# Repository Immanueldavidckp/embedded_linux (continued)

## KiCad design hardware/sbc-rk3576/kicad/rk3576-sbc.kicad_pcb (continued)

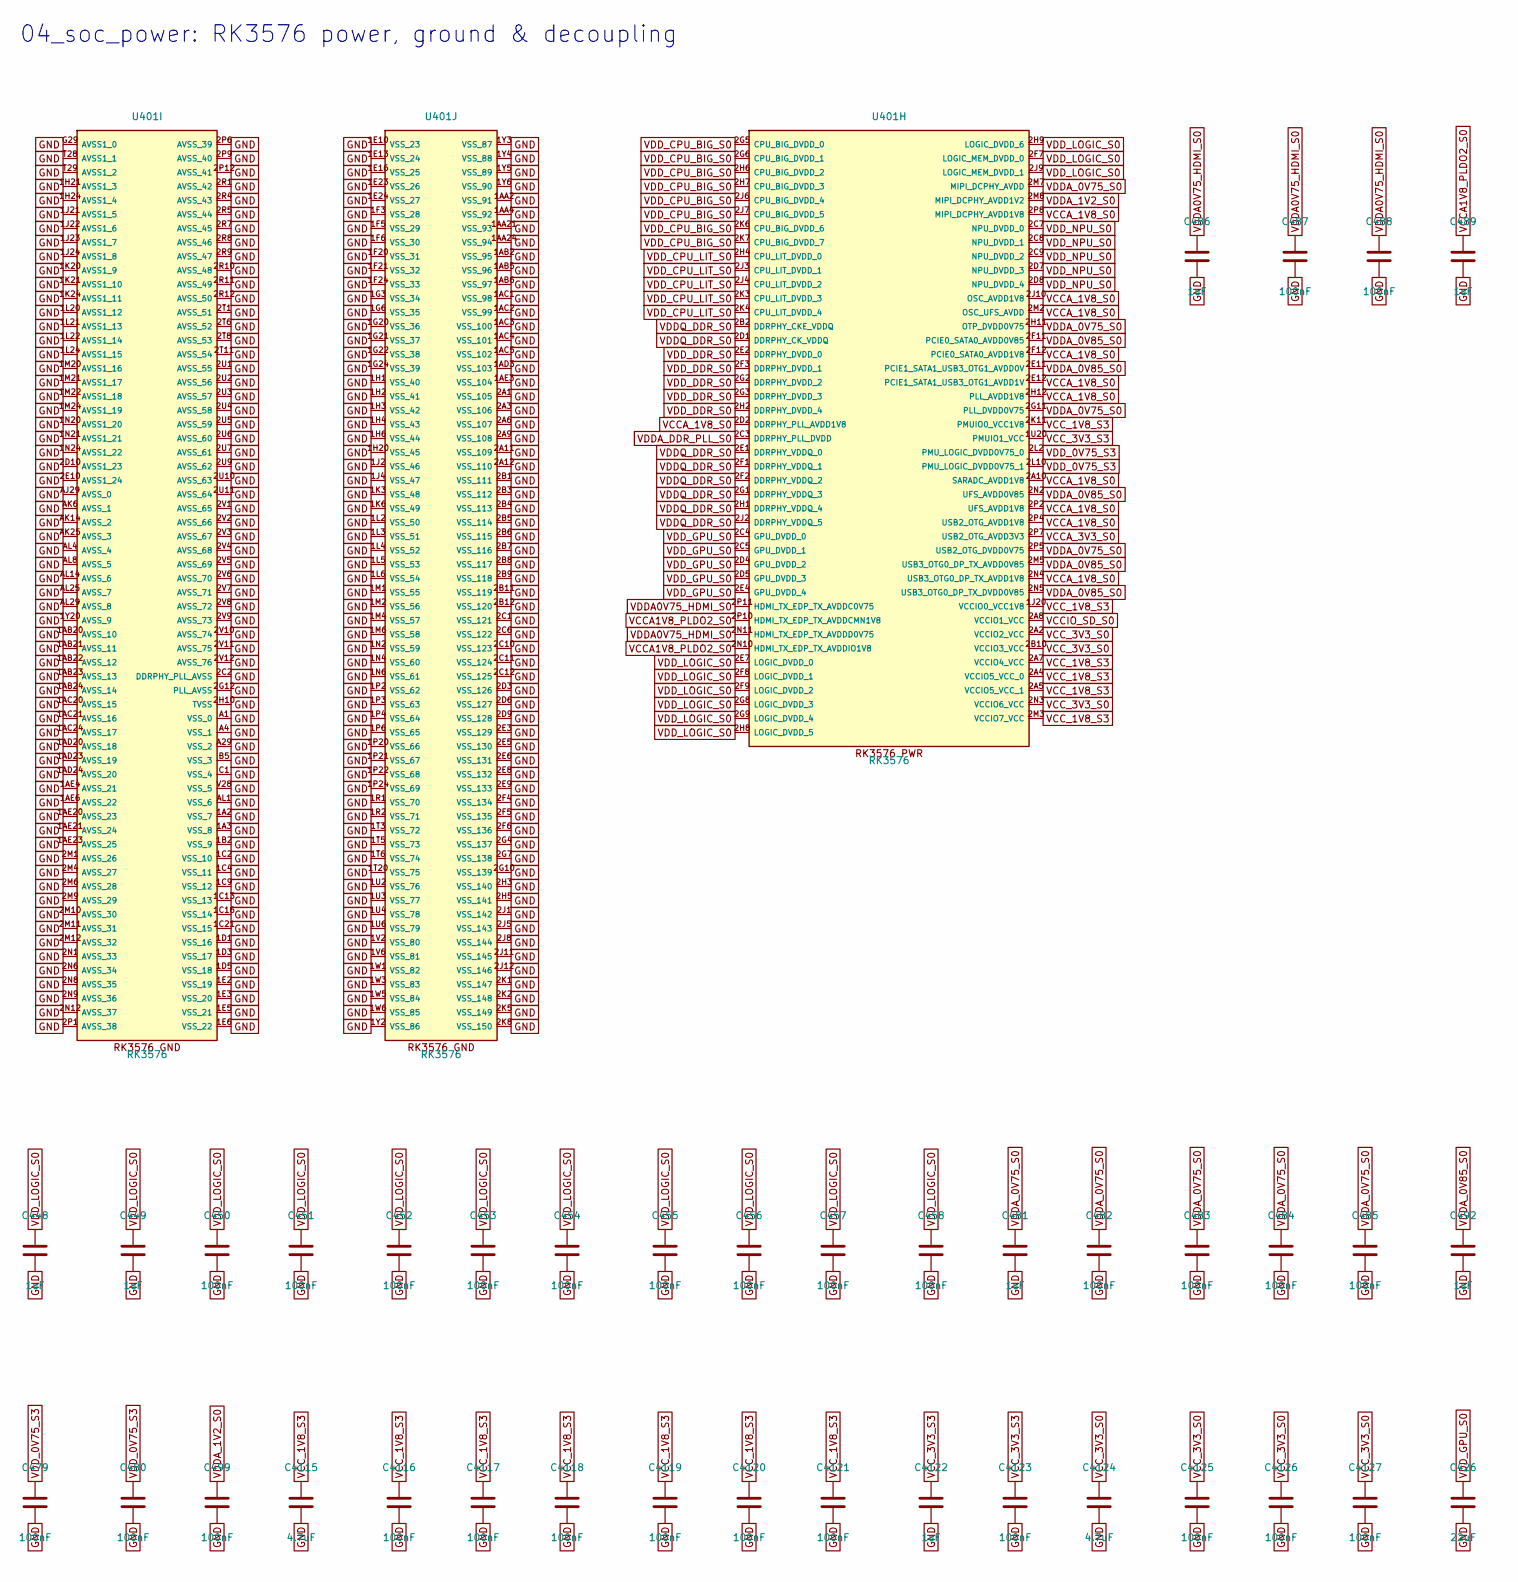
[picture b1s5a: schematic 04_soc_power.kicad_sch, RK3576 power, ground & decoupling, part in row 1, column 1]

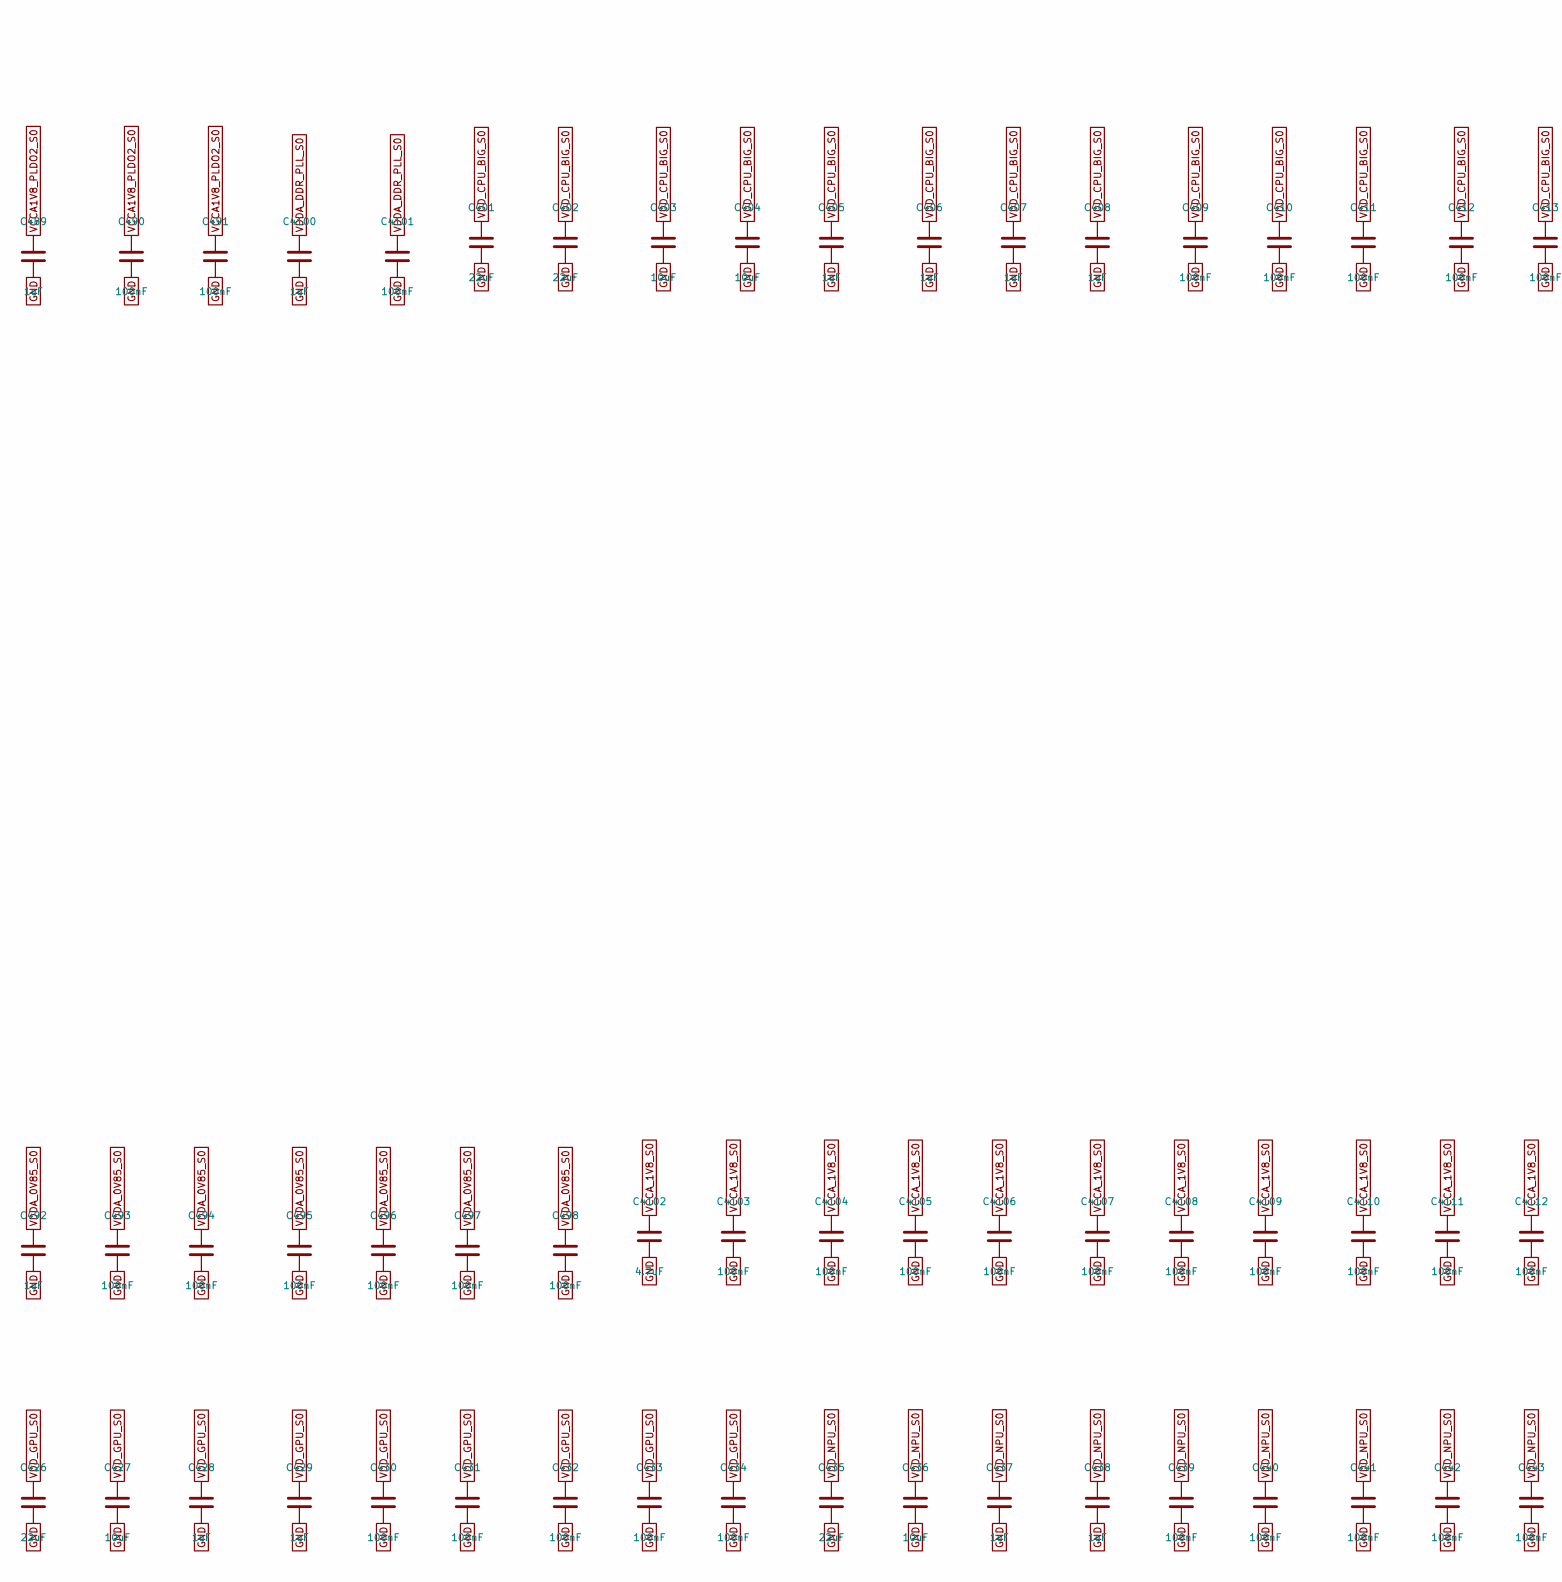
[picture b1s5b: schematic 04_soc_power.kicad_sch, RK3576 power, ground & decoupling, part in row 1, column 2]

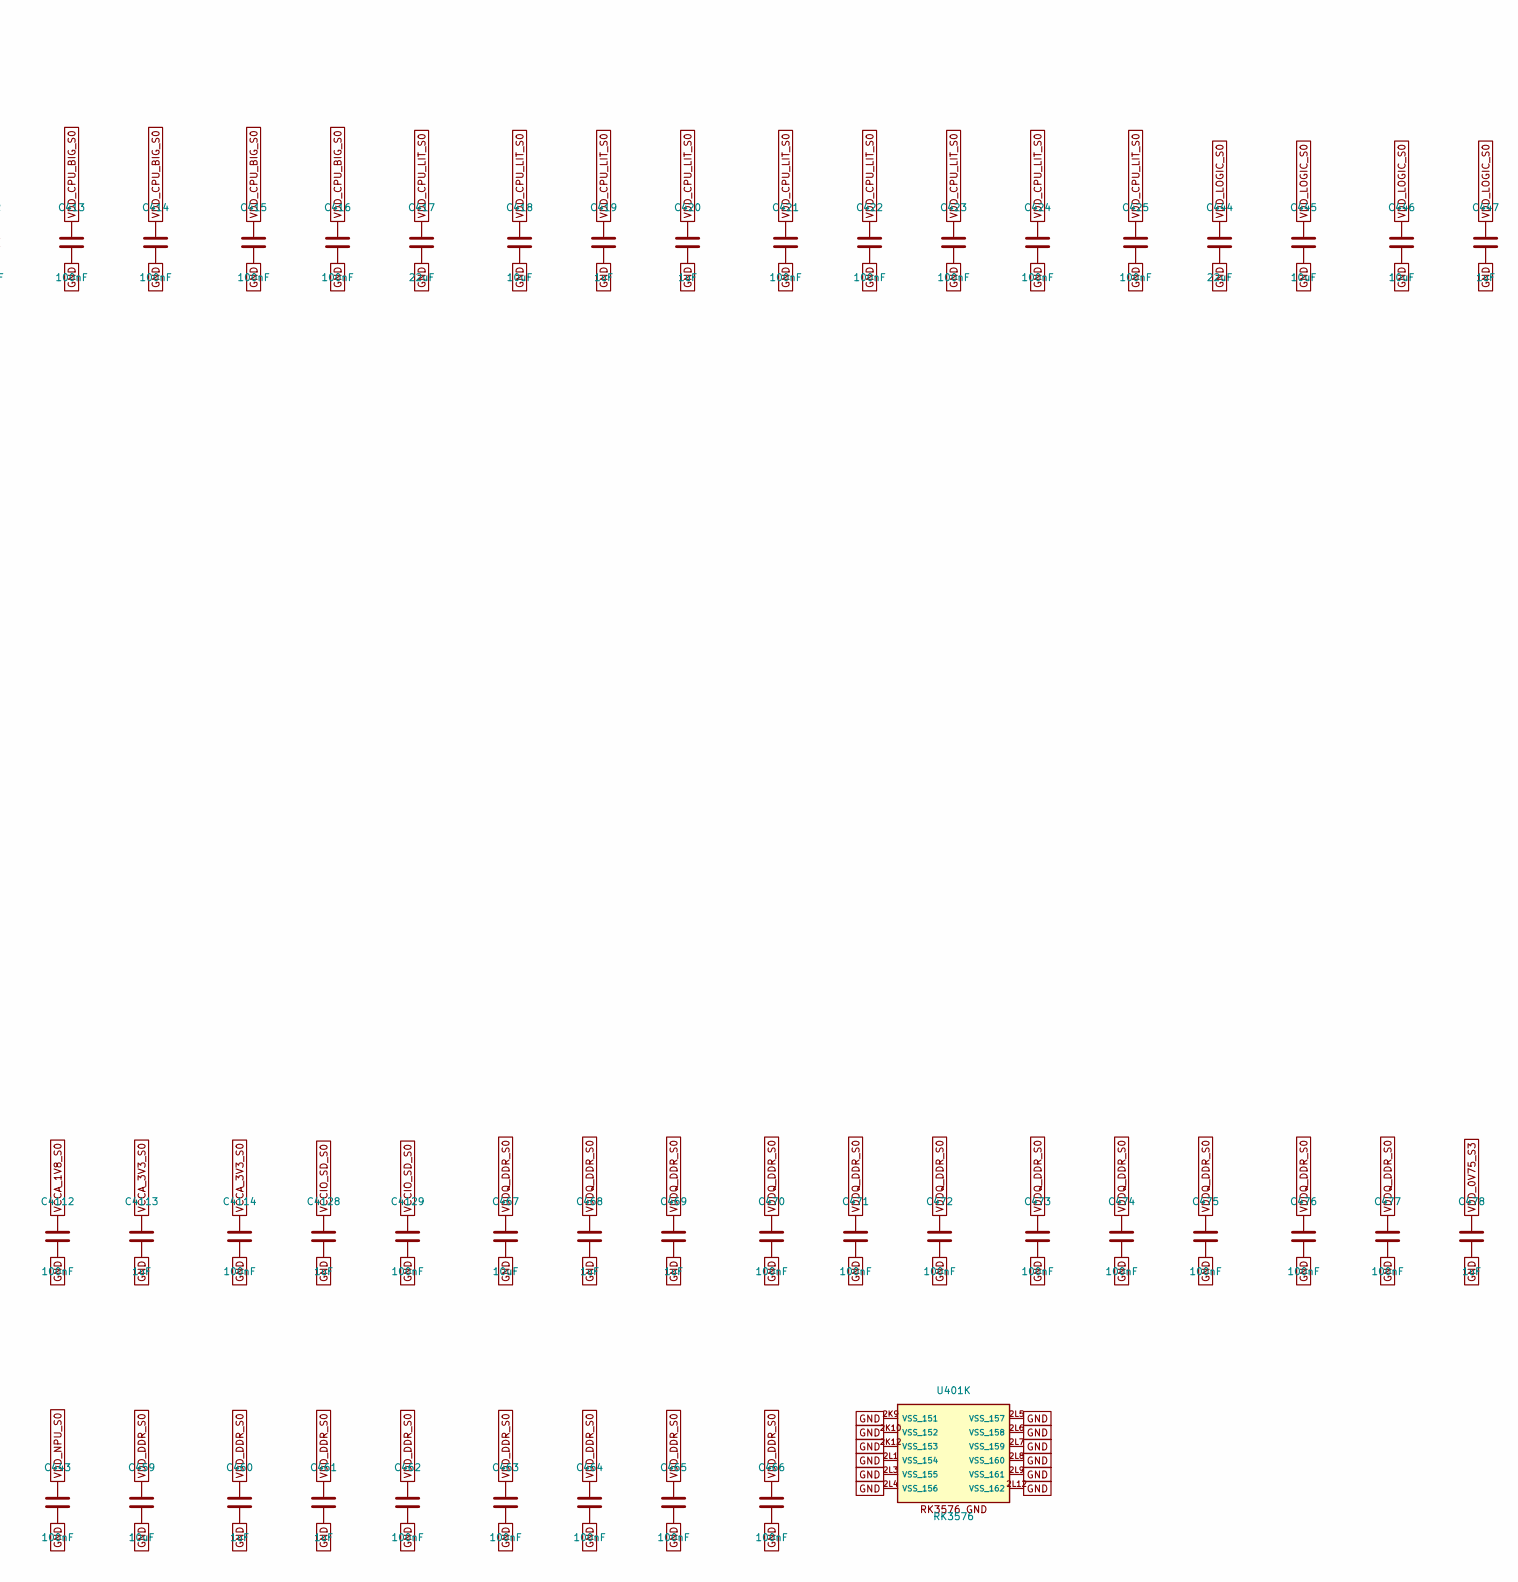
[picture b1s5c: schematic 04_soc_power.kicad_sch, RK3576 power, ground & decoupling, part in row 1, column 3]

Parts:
C401, C402, C417, C426, C435, C444: 22uF; C_0603_1608Metric; MPN 0603 22uF 10V X5R
C403, C404, C418, C427, C436, C445, C446, C459, C467: 10uF; C_0603_1608Metric; MPN 0603 10uF 10V X5R
C405, C406, C407, C408, C419, C420, C428, C429, C437, C438, C447, C448, C449, C460, C461, C468, C469, C478, C481, C486, C489, C492, C4100, C4113, C4122, C4128: 1uF; C_0402_1005Metric; MPN 0402 1uF 6.3V X5R
C409, C410, C411, C412, C413, C414, C415, C416, C421, C422, C423, C424, C425, C430, C431, C432, C433, C434, C439, C440, C441, C442, C443, C450, C451, C452, C453, C454, C455, C456, C457, C458, C462, C463, C464, C465, C466, C470, C471, C472, C473, C474, C475, C476, C477, C479, C480, C482, C483, C484, C485, C487, C488, C490, C491, C493, C494, C495, C496, C497, C498, C499, C4101, C4103, C4104, C4105, C4106, C4107, C4108, C4109, C4110, C4111, C4112, C4114, C4116, C4117, C4118, C4119, C4120, C4121, C4123, C4125, C4126, C4127, C4129: 100nF; C_0402_1005Metric; MPN 0402 100nF 6.3V X5R
C4102, C4115, C4124: 4.7uF; C_0402_1005Metric; MPN 0402 4.7uF 10V X5R
U401: RK3576; RK3576_FCCSP-698_16.1x17.2mm; MPN RK3576

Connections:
GND: C401.2, C402.2, C403.2, C404.2, C405.2, C406.2, C407.2, C408.2, C409.2, C410.2, C411.2, C412.2, C413.2, C414.2, C415.2, C416.2, C417.2, C418.2, C419.2, C420.2, C421.2, C422.2, C423.2, C424.2, C425.2, C426.2, C427.2, C428.2, C429.2, C430.2, C431.2, C432.2, C433.2, C434.2, C435.2, C436.2, C437.2, C438.2, C439.2, C440.2, C441.2, C442.2, C443.2, C444.2, C445.2, C446.2, C447.2, C448.2, C449.2, C450.2, C451.2, C452.2, C453.2, C454.2, C455.2, C456.2, C457.2, C458.2, C459.2, C460.2, C461.2, C462.2, C463.2, C464.2, C465.2, C466.2, C467.2, C468.2, C469.2, C470.2, C471.2, C472.2, C473.2, C474.2, C475.2, C476.2, C477.2, C478.2, C479.2, C480.2, C481.2, C482.2, C483.2, C484.2, C485.2, C486.2, C487.2, C488.2, C489.2, C490.2, C491.2, C492.2, C493.2, C494.2, C495.2, C496.2, C497.2, C498.2, C499.2, C4100.2, C4101.2, C4102.2, C4103.2, C4104.2, C4105.2, C4106.2, C4107.2, C4108.2, C4109.2, C4110.2, C4111.2, C4112.2, C4113.2, C4114.2, C4115.2, C4116.2, C4117.2, C4118.2, C4119.2, C4120.2, C4121.2, C4122.2, C4123.2, C4124.2, C4125.2, C4126.2, C4127.2, C4128.2, C4129.2, U401.1A2 (VSS_7), U401.1A3 (VSS_8), U401.1AA2 (VSS_91), U401.1AA4 (VSS_92), U401.1AA21 (VSS_93), U401.1AA24 (VSS_94), U401.1AB2 (VSS_95), U401.1AB5 (VSS_96), U401.1AB6 (VSS_97), U401.1AB20 (AVSS_10), U401.1AB21 (AVSS_11), U401.1AB22 (AVSS_12), U401.1AB23 (AVSS_13), U401.1AB24 (AVSS_14), U401.1AC1 (VSS_98), U401.1AC2 (VSS_99), U401.1AC3 (VSS_100), U401.1AC4 (VSS_101), U401.1AC5 (VSS_102), U401.1AC20 (AVSS_15), U401.1AC21 (AVSS_16), U401.1AC24 (AVSS_17), U401.1AD3 (VSS_103), U401.1AD20 (AVSS_18), U401.1AD23 (AVSS_19), U401.1AD24 (AVSS_20), U401.1AE3 (VSS_104), U401.1AE4 (AVSS_21), U401.1AE6 (AVSS_22), U401.1AE20 (AVSS_23), U401.1AE21 (AVSS_24), U401.1AE23 (AVSS_25), U401.1B2 (VSS_9), U401.1C2 (VSS_10), U401.1C4 (VSS_11), U401.1C9 (VSS_12), U401.1C13 (VSS_13), U401.1C16 (VSS_14), U401.1C21 (VSS_15), U401.1D1 (VSS_16), U401.1D3 (VSS_17), U401.1D5 (VSS_18), U401.1E2 (VSS_19), U401.1E3 (VSS_20), U401.1E5 (VSS_21), U401.1E6 (VSS_22), U401.1E10 (VSS_23), U401.1E13 (VSS_24), U401.1E16 (VSS_25), U401.1E23 (VSS_26), U401.1E24 (VSS_27), U401.1F3 (VSS_28), U401.1F5 (VSS_29), U401.1F6 (VSS_30), U401.1F20 (VSS_31), U401.1F21 (VSS_32), U401.1F24 (VSS_33), U401.1G3 (VSS_34), U401.1G6 (VSS_35), U401.1G20 (VSS_36), U401.1G21 (VSS_37), U401.1G22 (VSS_38), U401.1G24 (VSS_39), U401.1H1 (VSS_40), U401.1H2 (VSS_41), U401.1H3 (VSS_42), U401.1H4 (VSS_43), U401.1H6 (VSS_44), U401.1H20 (VSS_45), U401.1H21 (AVSS1_3), U401.1H24 (AVSS1_4), U401.1J2 (VSS_46), U401.1J4 (VSS_47), U401.1J21 (AVSS1_5), U401.1J22 (AVSS1_6), U401.1J23 (AVSS1_7), U401.1J24 (AVSS1_8), U401.1K3 (VSS_48), U401.1K6 (VSS_49), U401.1K20 (AVSS1_9), U401.1K21 (AVSS1_10), U401.1K24 (AVSS1_11), U401.1L2 (VSS_50), U401.1L3 (VSS_51), U401.1L4 (VSS_52), U401.1L5 (VSS_53), U401.1L6 (VSS_54), U401.1L20 (AVSS1_12), U401.1L21 (AVSS1_13), U401.1L22 (AVSS1_14), U401.1L24 (AVSS1_15), U401.1M1 (VSS_55), U401.1M2 (VSS_56), U401.1M4 (VSS_57), U401.1M6 (VSS_58), U401.1M20 (AVSS1_16), U401.1M21 (AVSS1_17), U401.1M22 (AVSS1_18), U401.1M24 (AVSS1_19), U401.1N2 (VSS_59), U401.1N4 (VSS_60), U401.1N6 (VSS_61), U401.1N20 (AVSS1_20), U401.1N21 (AVSS1_21), U401.1N24 (AVSS1_22), U401.1P2 (VSS_62), U401.1P3 (VSS_63), U401.1P4 (VSS_64), U401.1P6 (VSS_65), U401.1P20 (VSS_66), U401.1P21 (VSS_67), U401.1P22 (VSS_68), U401.1P24 (VSS_69), U401.1R1 (VSS_70), U401.1R2 (VSS_71), U401.1T3 (VSS_72), U401.1T5 (VSS_73), U401.1T6 (VSS_74), U401.1T20 (VSS_75), U401.1U2 (VSS_76), U401.1U3 (VSS_77), U401.1U4 (VSS_78), U401.1U6 (VSS_79), U401.1V2 (VSS_80), U401.1V6 (VSS_81), U401.1W1 (VSS_82), U401.1W3 (VSS_83), U401.1W5 (VSS_84), U401.1W6 (VSS_85), U401.1Y2 (VSS_86), U401.1Y3 (VSS_87), U401.1Y4 (VSS_88), U401.1Y5 (VSS_89), U401.1Y6 (VSS_90), U401.1Y20 (AVSS_9), U401.2A1 (VSS_105), U401.2A3 (VSS_106), U401.2A6 (VSS_107), U401.2A9 (VSS_108), U401.2A11 (VSS_109), U401.2A12 (VSS_110), U401.2B1 (VSS_111), U401.2B3 (VSS_112), U401.2B4 (VSS_113), U401.2B5 (VSS_114), U401.2B6 (VSS_115), U401.2B7 (VSS_116), U401.2B8 (VSS_117), U401.2B9 (VSS_118), U401.2B11 (VSS_119), U401.2B12 (VSS_120), U401.2C1 (VSS_121), U401.2C2 (DDRPHY_PLL_AVSS), U401.2C6 (VSS_122), U401.2C10 (VSS_123), U401.2C11 (VSS_124), U401.2C12 (VSS_125), U401.2D3 (VSS_126), U401.2D6 (VSS_127), U401.2D9 (VSS_128), U401.2D10 (AVSS1_23), U401.2E3 (VSS_129), U401.2E5 (VSS_130), U401.2E6 (VSS_131), U401.2E8 (VSS_132), U401.2E9 (VSS_133), U401.2E10 (AVSS1_24), U401.2F4 (VSS_134), U401.2F5 (VSS_135), U401.2F6 (VSS_136), U401.2G4 (VSS_137), U401.2G7 (VSS_138), U401.2G10 (VSS_139), U401.2G12 (PLL_AVSS), U401.2H3 (VSS_140), U401.2H5 (VSS_141), U401.2H10 (TVSS), U401.2J1 (VSS_142), U401.2J5 (VSS_143), U401.2J8 (VSS_144), U401.2J11 (VSS_145), U401.2J12 (VSS_146), U401.2K1 (VSS_147), U401.2K2 (VSS_148), U401.2K5 (VSS_149), U401.2K8 (VSS_150), U401.2K9 (VSS_151), U401.2K10 (VSS_152), U401.2K12 (VSS_153), U401.2L1 (VSS_154), U401.2L3 (VSS_155), U401.2L4 (VSS_156), U401.2L5 (VSS_157), U401.2L6 (VSS_158), U401.2L7 (VSS_159), U401.2L8 (VSS_160), U401.2L9 (VSS_161), U401.2L12 (VSS_162), U401.2M1 (AVSS_26), U401.2M4 (AVSS_27), U401.2M6 (AVSS_28), U401.2M9 (AVSS_29), U401.2M10 (AVSS_30), U401.2M11 (AVSS_31), U401.2M12 (AVSS_32), U401.2N1 (AVSS_33), U401.2N6 (AVSS_34), U401.2N8 (AVSS_35), U401.2N9 (AVSS_36), U401.2N12 (AVSS_37), U401.2P1 (AVSS_38), U401.2P6 (AVSS_39), U401.2P9 (AVSS_40), U401.2P12 (AVSS_41), U401.2R1 (AVSS_42), U401.2R4 (AVSS_43), U401.2R5 (AVSS_44), U401.2R7 (AVSS_45), U401.2R8 (AVSS_46), U401.2R9 (AVSS_47), U401.2R10 (AVSS_48), U401.2R11 (AVSS_49), U401.2R12 (AVSS_50), U401.2T1 (AVSS_51), U401.2T6 (AVSS_52), U401.2T8 (AVSS_53), U401.2T11 (AVSS_54), U401.2U1 (AVSS_55), U401.2U2 (AVSS_56), U401.2U3 (AVSS_57), U401.2U4 (AVSS_58), U401.2U5 (AVSS_59), U401.2U6 (AVSS_60), U401.2U7 (AVSS_61), U401.2U9 (AVSS_62), U401.2U10 (AVSS_63), U401.2U11 (AVSS_64), U401.2V1 (AVSS_65), U401.2V2 (AVSS_66), U401.2V3 (AVSS_67), U401.2V4 (AVSS_68), U401.2V5 (AVSS_69), U401.2V6 (AVSS_70), U401.2V7 (AVSS_71), U401.2V8 (AVSS_72), U401.2V9 (AVSS_73), U401.2V10 (AVSS_74), U401.2V11 (AVSS_75), U401.2V12 (AVSS_76), U401.A1 (VSS_0), U401.A4 (VSS_1), U401.A29 (VSS_2), U401.AJ29 (AVSS_0), U401.AK6 (AVSS_1), U401.AK14 (AVSS_2), U401.AK25 (AVSS_3), U401.AL1 (VSS_6), U401.AL4 (AVSS_4), U401.AL8 (AVSS_5), U401.AL14 (AVSS_6), U401.AL25 (AVSS_7), U401.AL29 (AVSS_8), U401.B5 (VSS_3), U401.C1 (VSS_4), U401.G29 (AVSS1_0), U401.T28 (AVSS1_1), U401.T29 (AVSS1_2), U401.V28 (VSS_5); also elsewhere on the board
VCCA1V8_PLDO2_S0: C489.1, C490.1, C491.1, U401.2N10 (HDMI_TX_EDP_TX_AVDDIO1V8), U401.2P10 (HDMI_TX_EDP_TX_AVDDCMN1V8); also elsewhere on the board
VCCA_1V8_S0: C4102.1, C4103.1, C4104.1, C4105.1, C4106.1, C4107.1, C4108.1, C4109.1, C4110.1, C4111.1, C4112.1, U401.2A10 (SARADC_AVDD1V8), U401.2D2 (DDRPHY_PLL_AVDD1V8), U401.2E12 (PCIE1_SATA1_USB3_OTG1_AVDD1V), U401.2F12 (PCIE0_SATA0_AVDD1V8), U401.2H12 (PLL_AVDD1V8), U401.2J10 (OSC_AVDD1V8), U401.2M2 (OSC_UFS_AVDD), U401.2N4 (USB3_OTG0_DP_TX_AVDD1V8), U401.2P2 (UFS_AVDD1V8), U401.2P4 (USB2_OTG_AVDD1V8), U401.2P8 (MIPI_DCPHY_AVDD1V8); also elsewhere on the board
VCCA_3V3_S0: C4113.1, C4114.1, U401.2P7 (USB2_OTG_AVDD3V3); also elsewhere on the board
VCCIO_SD_S0: C4128.1, C4129.1, U401.2A8 (VCCIO1_VCC); also elsewhere on the board
VCC_1V8_S3: C4115.1, C4116.1, C4117.1, C4118.1, C4119.1, C4120.1, C4121.1, U401.1J20 (VCCIO0_VCC1V8), U401.2A4 (VCCIO5_VCC_0), U401.2A5 (VCCIO5_VCC_1), U401.2A7 (VCCIO4_VCC), U401.2K11 (PMUIO0_VCC1V8), U401.2M3 (VCCIO7_VCC); also elsewhere on the board
VCC_3V3_S0: C4124.1, C4125.1, C4126.1, C4127.1, U401.2A2 (VCCIO2_VCC), U401.2B10 (VCCIO3_VCC), U401.2N3 (VCCIO6_VCC); also elsewhere on the board
VCC_3V3_S3: C4122.1, C4123.1, U401.1U20 (PMUIO1_VCC); also elsewhere on the board
VDDA0V75_HDMI_S0: C486.1, C487.1, C488.1, U401.2N11 (HDMI_TX_EDP_TX_AVDDD0V75), U401.2P11 (HDMI_TX_EDP_TX_AVDDC0V75); also elsewhere on the board
VDDA_0V75_S0: C481.1, C482.1, C483.1, C484.1, C485.1, U401.2G11 (PLL_DVDD0V75), U401.2H11 (OTP_DVDD0V75), U401.2M7 (MIPI_DCPHY_AVDD), U401.2P5 (USB2_OTG_DVDD0V75); also elsewhere on the board
VDDA_0V85_S0: C492.1, C493.1, C494.1, C495.1, C496.1, C497.1, C498.1, U401.2E11 (PCIE1_SATA1_USB3_OTG1_AVDD0V), U401.2F11 (PCIE0_SATA0_AVDD0V85), U401.2M5 (USB3_OTG0_DP_TX_AVDD0V85), U401.2N2 (UFS_AVDD0V85), U401.2N5 (USB3_OTG0_DP_TX_DVDD0V85); also elsewhere on the board
VDDA_1V2_S0: C499.1, U401.2M8 (MIPI_DCPHY_AVDD1V2); also elsewhere on the board
VDDA_DDR_PLL_S0: C4100.1, C4101.1, U401.2C3 (DDRPHY_PLL_DVDD); also elsewhere on the board
VDDQ_DDR_S0: C467.1, C468.1, C469.1, C470.1, C471.1, C472.1, C473.1, C474.1, C475.1, C476.1, C477.1, U401.2B2 (DDRPHY_CKE_VDDQ), U401.2D1 (DDRPHY_CK_VDDQ), U401.2E1 (DDRPHY_VDDQ_0), U401.2F1 (DDRPHY_VDDQ_1), U401.2F2 (DDRPHY_VDDQ_2), U401.2G1 (DDRPHY_VDDQ_3), U401.2H1 (DDRPHY_VDDQ_4), U401.2J2 (DDRPHY_VDDQ_5); also elsewhere on the board
VDD_0V75_S3: C478.1, C479.1, C480.1, U401.2L2 (PMU_LOGIC_DVDD0V75_0), U401.2L10 (PMU_LOGIC_DVDD0V75_1); also elsewhere on the board
VDD_CPU_BIG_S0: C401.1, C402.1, C403.1, C404.1, C405.1, C406.1, C407.1, C408.1, C409.1, C410.1, C411.1, C412.1, C413.1, C414.1, C415.1, C416.1, U401.2G5 (CPU_BIG_DVDD_0), U401.2G6 (CPU_BIG_DVDD_1), U401.2H6 (CPU_BIG_DVDD_2), U401.2H7 (CPU_BIG_DVDD_3), U401.2J6 (CPU_BIG_DVDD_4), U401.2J7 (CPU_BIG_DVDD_5), U401.2K6 (CPU_BIG_DVDD_6), U401.2K7 (CPU_BIG_DVDD_7); also elsewhere on the board
VDD_CPU_LIT_S0: C417.1, C418.1, C419.1, C420.1, C421.1, C422.1, C423.1, C424.1, C425.1, U401.2H4 (CPU_LIT_DVDD_0), U401.2J3 (CPU_LIT_DVDD_1), U401.2J4 (CPU_LIT_DVDD_2), U401.2K3 (CPU_LIT_DVDD_3), U401.2K4 (CPU_LIT_DVDD_4); also elsewhere on the board
VDD_DDR_S0: C459.1, C460.1, C461.1, C462.1, C463.1, C464.1, C465.1, C466.1, U401.2E2 (DDRPHY_DVDD_0), U401.2F3 (DDRPHY_DVDD_1), U401.2G2 (DDRPHY_DVDD_2), U401.2G3 (DDRPHY_DVDD_3), U401.2H2 (DDRPHY_DVDD_4); also elsewhere on the board
VDD_GPU_S0: C426.1, C427.1, C428.1, C429.1, C430.1, C431.1, C432.1, C433.1, C434.1, U401.2C4 (GPU_DVDD_0), U401.2C5 (GPU_DVDD_1), U401.2D4 (GPU_DVDD_2), U401.2D5 (GPU_DVDD_3), U401.2E4 (GPU_DVDD_4); also elsewhere on the board
VDD_LOGIC_S0: C444.1, C445.1, C446.1, C447.1, C448.1, C449.1, C450.1, C451.1, C452.1, C453.1, C454.1, C455.1, C456.1, C457.1, C458.1, U401.2E7 (LOGIC_DVDD_0), U401.2F7 (LOGIC_MEM_DVDD_0), U401.2F8 (LOGIC_DVDD_1), U401.2F9 (LOGIC_DVDD_2), U401.2G8 (LOGIC_DVDD_3), U401.2G9 (LOGIC_DVDD_4), U401.2H8 (LOGIC_DVDD_5), U401.2H9 (LOGIC_DVDD_6), U401.2J9 (LOGIC_MEM_DVDD_1); also elsewhere on the board
VDD_NPU_S0: C435.1, C436.1, C437.1, C438.1, C439.1, C440.1, C441.1, C442.1, C443.1, U401.2C7 (NPU_DVDD_0), U401.2C8 (NPU_DVDD_1), U401.2C9 (NPU_DVDD_2), U401.2D7 (NPU_DVDD_3), U401.2D8 (NPU_DVDD_4); also elsewhere on the board

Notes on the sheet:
04_soc_power: RK3576 power, ground & decoupling

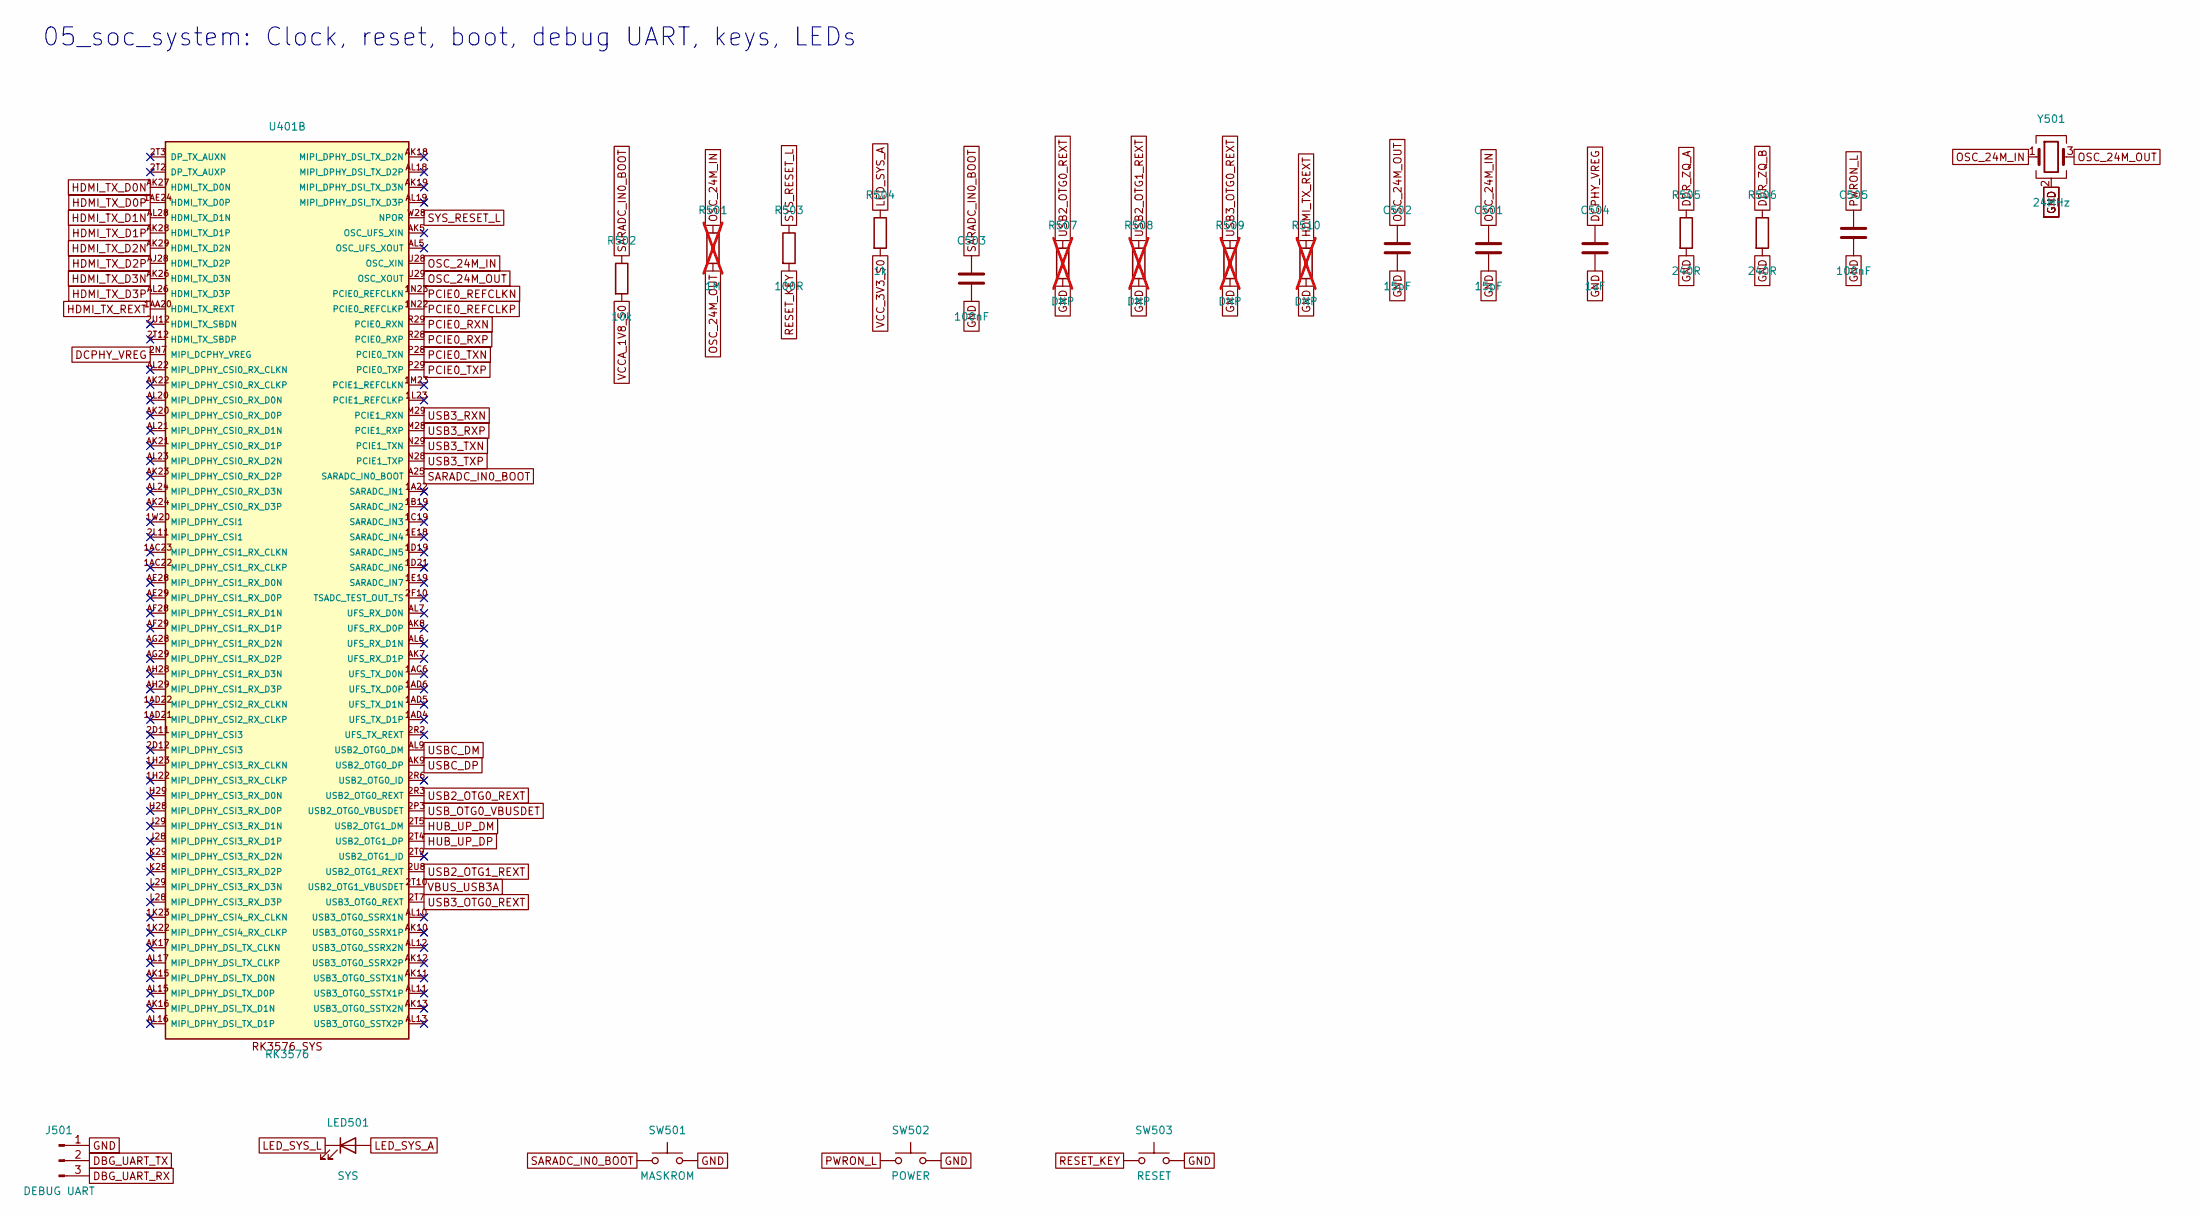
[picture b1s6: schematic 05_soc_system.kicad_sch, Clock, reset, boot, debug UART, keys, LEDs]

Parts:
C501, C502: 15pF; C_0402_1005Metric; MPN 0402 15pF 50V C0G
C503, C505: 100nF; C_0402_1005Metric; MPN 0402 100nF 6.3V X5R
C504: 1uF; C_0402_1005Metric; MPN 0402 1uF 6.3V X5R
J501: DEBUG UART; PinHeader_1x03_P2.54mm_Vertical; MPN 2.54mm 1x3 pin header
LED501: SYS; LED_0603_1608Metric; MPN 19-217/BHC-ZL1M2RY/3T; LCSC C72041
R501: 1M; R_0402_1005Metric; MPN 0402 1M 1%; not fitted
R502: 10k; R_0402_1005Metric; MPN 0402 10k 1%
R503: 100R; R_0402_1005Metric; MPN 0402 100R 1%
R504: 1k; R_0402_1005Metric; MPN 0402 1k 1%
R505, R506: 240R; R_0402_1005Metric; MPN 0402 240R 1%
R507, R508, R509, R510: DNP; R_0402_1005Metric; MPN 0402 DNP 1%; not fitted
SW501: MASKROM; SW_SPST_PTS810; MPN PTS810 SJM 250 SMTR LFS (alt XKB TS-108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
SW502: POWER; SW_SPST_PTS810; MPN PTS810 SJM 250 SMTR LFS (alt XKB TS-108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
SW503: RESET; SW_SPST_PTS810; MPN PTS810 SJM 250 SMTR LFS (alt XKB TS-108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
U401: RK3576; RK3576_FCCSP-698_16.1x17.2mm; MPN RK3576
Y501: 24MHz; Crystal_SMD_3225-4Pin_3.2x2.5mm; MPN X322524MOB4SI (24MHz 20pF 10ppm); LCSC C9002

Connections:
DBG_UART_RX: J501.3; also elsewhere on the board
DBG_UART_TX: J501.2; also elsewhere on the board
DCPHY_VREG: C504.1, U401.2N7 (MIPI_DCPHY_VREG)
DDR_ZQ_A: R505.1; also elsewhere on the board
DDR_ZQ_B: R506.1; also elsewhere on the board
GND: C501.2, C502.2, C503.2, C504.2, C505.2, J501.1, R505.2, R506.2, R507.2, R508.2, R509.2, R510.2, SW501.2, SW502.2, SW503.2, Y501.2 (G), Y501.4 (G); also elsewhere on the board
HDMI_TX_D0N: U401.AK27 (HDMI_TX_D0N); also elsewhere on the board
HDMI_TX_D0P: U401.1AE24 (HDMI_TX_D0P); also elsewhere on the board
HDMI_TX_D1N: U401.AL28 (HDMI_TX_D1N); also elsewhere on the board
HDMI_TX_D1P: U401.AK28 (HDMI_TX_D1P); also elsewhere on the board
HDMI_TX_D2N: U401.AK29 (HDMI_TX_D2N); also elsewhere on the board
HDMI_TX_D2P: U401.AJ28 (HDMI_TX_D2P); also elsewhere on the board
HDMI_TX_D3N: U401.AK26 (HDMI_TX_D3N); also elsewhere on the board
HDMI_TX_D3P: U401.AL26 (HDMI_TX_D3P); also elsewhere on the board
HDMI_TX_REXT: R510.1, U401.1AA20 (HDMI_TX_REXT)
HUB_UP_DM: U401.2T5 (USB2_OTG1_DM); also elsewhere on the board
HUB_UP_DP: U401.2T4 (USB2_OTG1_DP); also elsewhere on the board
LED_SYS_A: LED501.2 (A), R504.1
LED_SYS_L: LED501.1 (K); also elsewhere on the board
OSC_24M_IN: C501.1, R501.1, U401.U28 (OSC_XIN), Y501.1
OSC_24M_OUT: C502.1, R501.2, U401.U29 (OSC_XOUT), Y501.3
PCIE0_REFCLKN: U401.1N23 (PCIE0_REFCLKN); also elsewhere on the board
PCIE0_REFCLKP: U401.1N22 (PCIE0_REFCLKP); also elsewhere on the board
PCIE0_RXN: U401.R29 (PCIE0_RXN); also elsewhere on the board
PCIE0_RXP: U401.R28 (PCIE0_RXP); also elsewhere on the board
PCIE0_TXN: U401.P28 (PCIE0_TXN); also elsewhere on the board
PCIE0_TXP: U401.P29 (PCIE0_TXP); also elsewhere on the board
PWRON_L: C505.1, SW502.1; also elsewhere on the board
RESET_KEY: R503.2, SW503.1
SARADC_IN0_BOOT: C503.1, R502.1, SW501.1, U401.A25 (SARADC_IN0_BOOT)
SYS_RESET_L: R503.1, U401.W28 (NPOR); also elsewhere on the board
USB2_OTG0_REXT: R507.1, U401.2R3 (USB2_OTG0_REXT)
USB2_OTG1_REXT: R508.1, U401.2U8 (USB2_OTG1_REXT)
USB3_OTG0_REXT: R509.1, U401.2T7 (USB3_OTG0_REXT)
USB3_RXN: U401.M29 (PCIE1_RXN); also elsewhere on the board
USB3_RXP: U401.M28 (PCIE1_RXP); also elsewhere on the board
USB3_TXN: U401.N29 (PCIE1_TXN); also elsewhere on the board
USB3_TXP: U401.N28 (PCIE1_TXP); also elsewhere on the board
USBC_DM: U401.AL9 (USB2_OTG0_DM); also elsewhere on the board
USBC_DP: U401.AK9 (USB2_OTG0_DP); also elsewhere on the board
USB_OTG0_VBUSDET: U401.2P3 (USB2_OTG0_VBUSDET); also elsewhere on the board
VBUS_USB3A: U401.2T10 (USB2_OTG1_VBUSDET); also elsewhere on the board
VCCA_1V8_S0: R502.2; also elsewhere on the board
VCC_3V3_S0: R504.2; also elsewhere on the board

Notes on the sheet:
05_soc_system: Clock, reset, boot, debug UART, keys, LEDs
